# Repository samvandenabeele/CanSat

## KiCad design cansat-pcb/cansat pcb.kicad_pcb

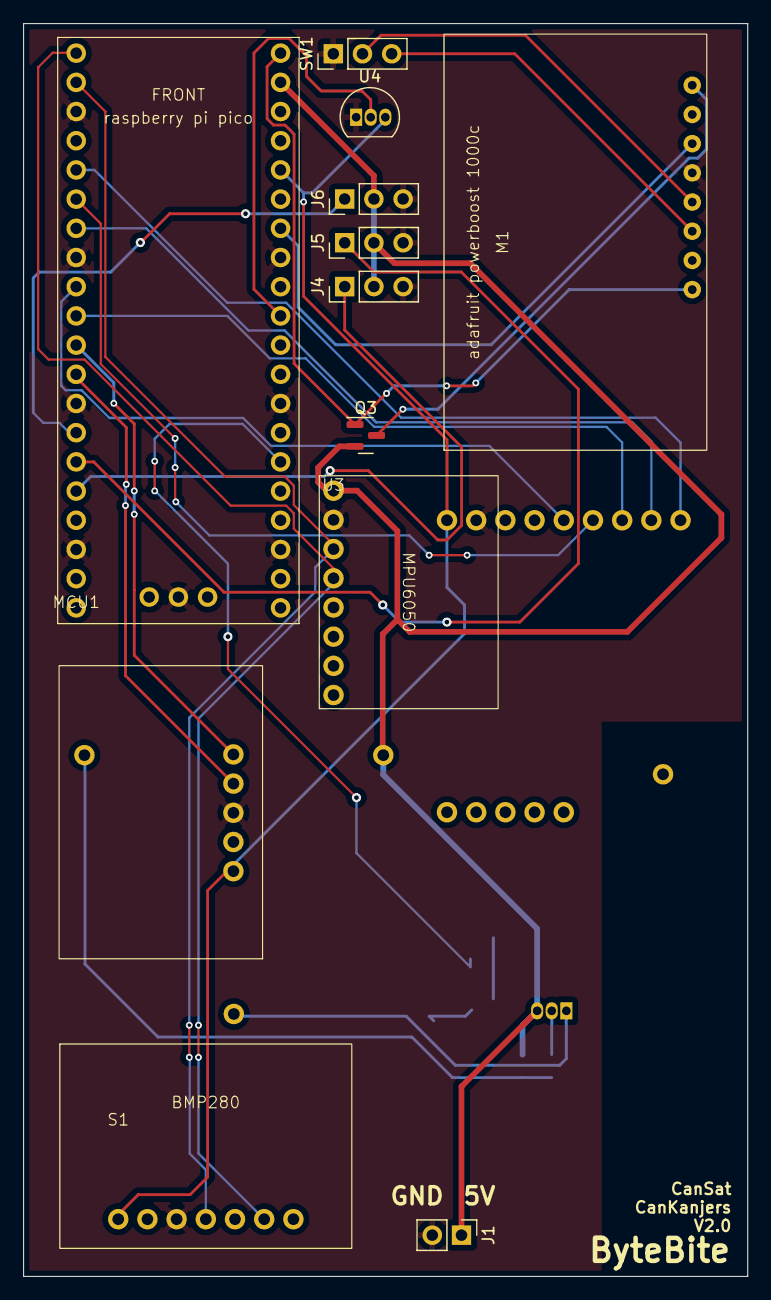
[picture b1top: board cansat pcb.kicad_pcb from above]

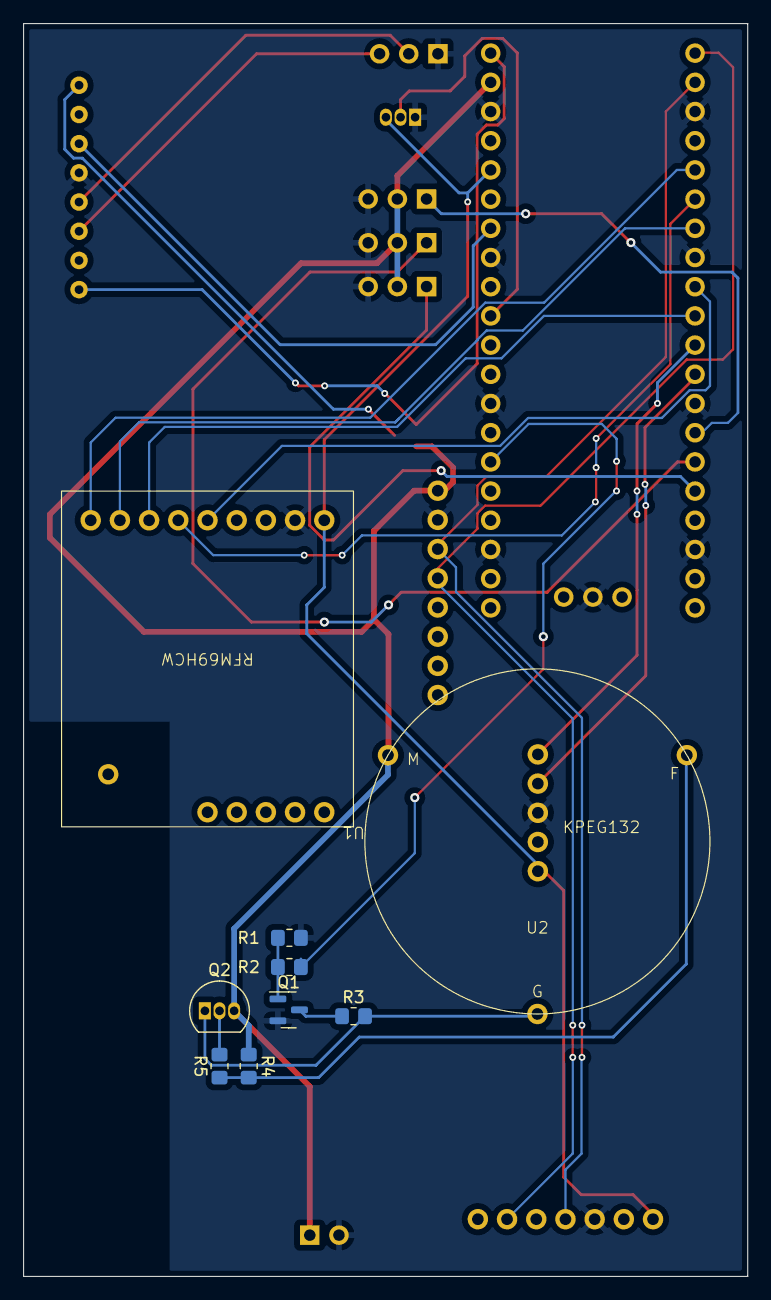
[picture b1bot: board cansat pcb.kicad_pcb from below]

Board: 2 copper layers, 63.0 x 109.0 mm, 21 parts (9 on the bottom side), 27 nets.

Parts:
J1: Conn_01x02_Pin; PinHeader_1x02_P2.54mm_Vertical
J4, J5, J6: Conn_01x03_Pin; PinHeader_1x03_P2.54mm_Vertical
M1: PowerBoost
MCU1: raspberry pi pico
Q1: AO3400A; SOT-23
Q2: 2N3904; TO-92_Inline
Q3: DMG2301L; SOT-23
R1, R4: 100K; R_0805_2012Metric_Pad1.20x1.40mm_HandSolder
R2, R3: 1K; R_0805_2012Metric_Pad1.20x1.40mm_HandSolder
R5: 22K; R_0805_2012Metric_Pad1.20x1.40mm_HandSolder
S1: BMP280
SW1: SW_DPDT_x2; PinHeader_1x03_P2.54mm_Vertical
U1: RFM69HCW
U2: KPEG132
U3: MPU6050
U4: TO-92L_Inline
U5: SGP30

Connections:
+3V3: MCU1.36 (3V3(OUT)), S1.1 (VIN), U1.1 (VIN), U4.3 (VIN), U5.1 (VIN)
+5V: J1.1, J4.2, J5.2, J6.2, MCU1.39 (VSYS), Q2.3 (C), Q3.2 (S), R4.1, U2.2 (M), U3.1 (VIN)
/SERVO/SERVO 1: J4.1, MCU1.16 (GP12)
/SERVO/SERVO 2: J5.1, MCU1.15 (GP11)
/SERVO/SERVO 3: J6.1, MCU1.14 (GP10)
/buzzer: MCU1.26 (GP20), R2.2
CS: MCU1.7 (GP5), U1.8 (CS)
EN_PB: M1.4 (EN), SW1.2 (B)
GND: J1.2, J4.3, J5.3, J6.3, M1.5 (GND), MCU1.3 (GND), MCU1.8 (GND), MCU1.13 (GND), MCU1.18 (GND), MCU1.23 (GND), MCU1.28 (GND), MCU1.33 (GND), MCU1.38 (GND), MCU1.42 (GND), Q1.2 (S), R1.1, S1.3 (GND), SW1.1 (A), U1.2 (GND), U3.2 (GND), U4.1 (GND), U5.3 (GND)
I2C0 SCL: MCU1.2 (GP1), S1.4 (SCK), U3.3 (SCL)
I2C0 SDA: MCU1.1 (GP0), S1.6 (SDI), U3.4 (SDA)
I2C1 SCL: MCU1.12 (GP9), U5.4 (SCL)
I2C1 SDA: MCU1.11 (GP8), U5.5 (SDA)
LBO_PB: M1.6 (LBO), MCU1.34 (GP28)
MISO: MCU1.6 (GP4), U1.6 (MISO)
MOSI: MCU1.10 (GP7), U1.7 (MOSI)
unnamed: M1.8 (5V), Q3.3 (D)
unnamed: Q1.3 (D), R3.1
unnamed: Q1.1 (G), R1.2, R2.1
unnamed: Q2.2 (B), R5.2
unnamed: Q2.1 (E), R3.2, U2.3 (G)
unnamed: R4.2, R5.1, U2.1 (F)
RST: MCU1.5 (GP3), U1.9 (RST)
SCK: MCU1.9 (GP6), U1.5 (SCK)
TMP1: MCU1.31 (GP26), U4.2 (VOUT)
VBUS: M1.1 (USB), MCU1.40 (VBUS), Q3.1 (G)
VS_PB: M1.3 (VS), SW1.3 (C)

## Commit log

2024-12-27 cleanup
2024-12-29 starting point
2025-01-04 Add sensor modules and update main script
    - Added new sensor modules: BMP280, MPU6050, RFM69
    - Deleted old BMP280_X.py file
    - Updated main.py to integrate new sensor modules
2025-01-05 completed libraries
2025-01-05 not much
    Nothing I believe
2025-01-05 Add MPU6050 sensor integration and RFM69 receive method
2025-01-05 LAATSTE VERSIE!!!!!!
2025-01-05 Start of transmitting data (by use of time intervals)
2025-01-05 created MARKDOWN.md
2025-01-05 added library files
2025-01-05 Revert "added library files"
    This reverts commit eb7502acf5d66833e683280658e26b31e38cade0.
2025-01-05 initialising Ground station
2025-01-08 sgp30 driver
2025-01-09 made some changes to pcb (fuck you Berenger)
2025-01-12 Revert "Merge commit '673e45e53089288ec36ae3b7f805afa0fd734616'"
    This reverts commit 0ed28d3d5ac29bb0831e5b0937f54a526884ff85, reversing
    changes made to 753dbbe2e9bb9dc030257394465552912bba7aea.
2025-01-12 pcb done
2025-01-16 pcb desing + TMP36 class
2025-02-10 completed imports
2025-02-10 added imports
2025-03-22 pcb V2
2025-04-01 groundstation test code
2025-04-01 simplify packet reception logging by removing unnecessary print statements
2025-04-01 add bootstrap script and new libraries for servo and vector3d functionality
2025-04-14 add initial PCB design file for CanSat components
2025-04-14 created a program that listens for the receiving pico to print something and then plots that data in a graph
2025-04-17 Add GPS functionality and integrate MicropyGPS for location tracking
2025-04-18 Dago doet iets (wss nog steeds slecht)
    1. in Main, kleine filter opgesteld voor het versturen van de data
    2. in ground station, Kalman filter opgesteld (kan zeker fout zijn, moet nog eens deftig naar gekeken worden, ik ben géén pro.
    3. plots ingesteld, daar kijk ik wel nog eens naar met meneer Vanholme, hij heeft veel ervaring.
    -> er zitten ongetwijfeld fouten in ,maar toch zeg het als je iets verandert, zo leer ik ook hé =)
2025-04-20 fix typo
2025-04-20 delete the plotting code that was not properly located. To make sure this does not happen again, I request that you learn to use issues and pull requests on GitHub. This will help us keep track of ch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
    @Dagorius
2025-04-20 Create LICENSE
